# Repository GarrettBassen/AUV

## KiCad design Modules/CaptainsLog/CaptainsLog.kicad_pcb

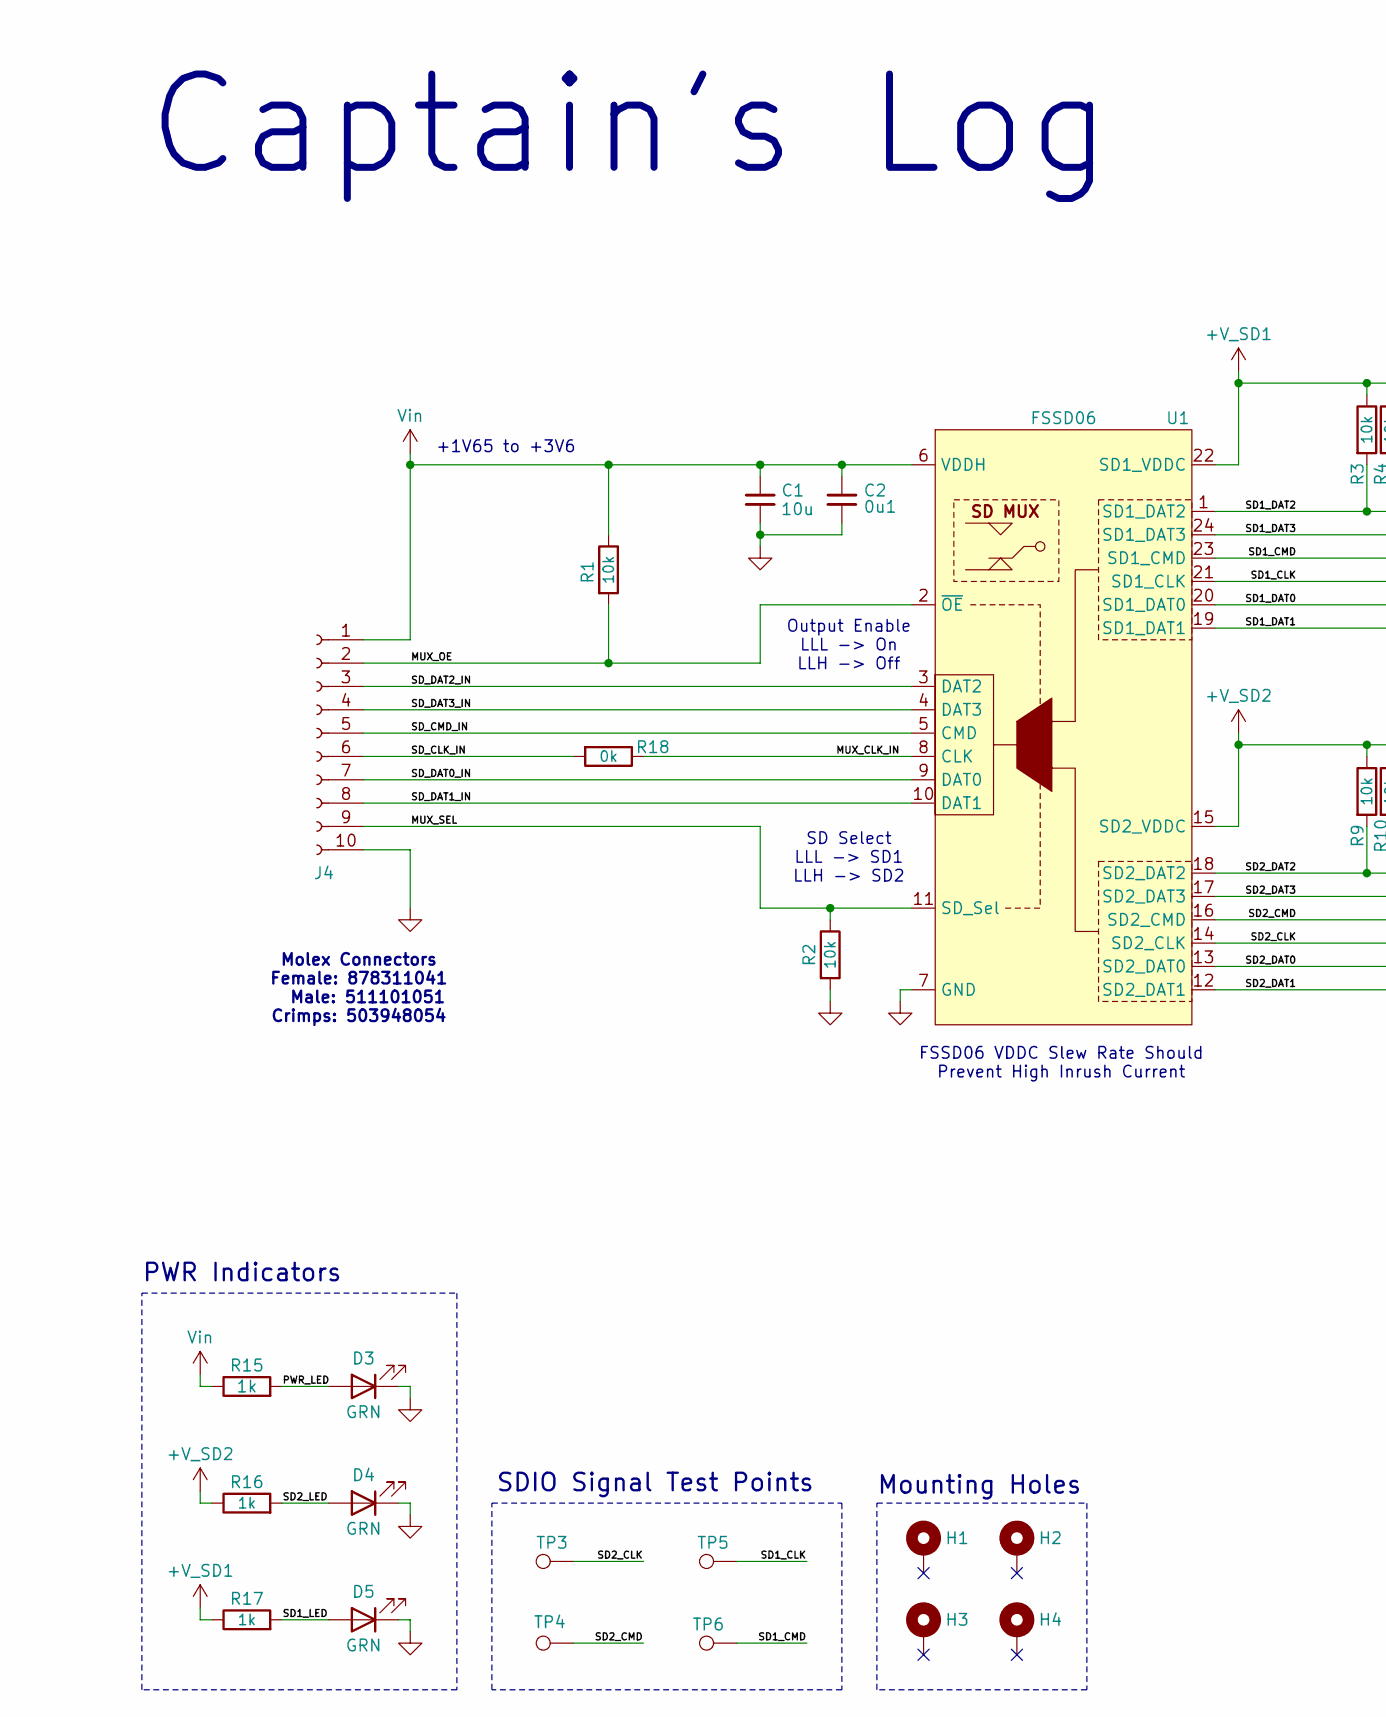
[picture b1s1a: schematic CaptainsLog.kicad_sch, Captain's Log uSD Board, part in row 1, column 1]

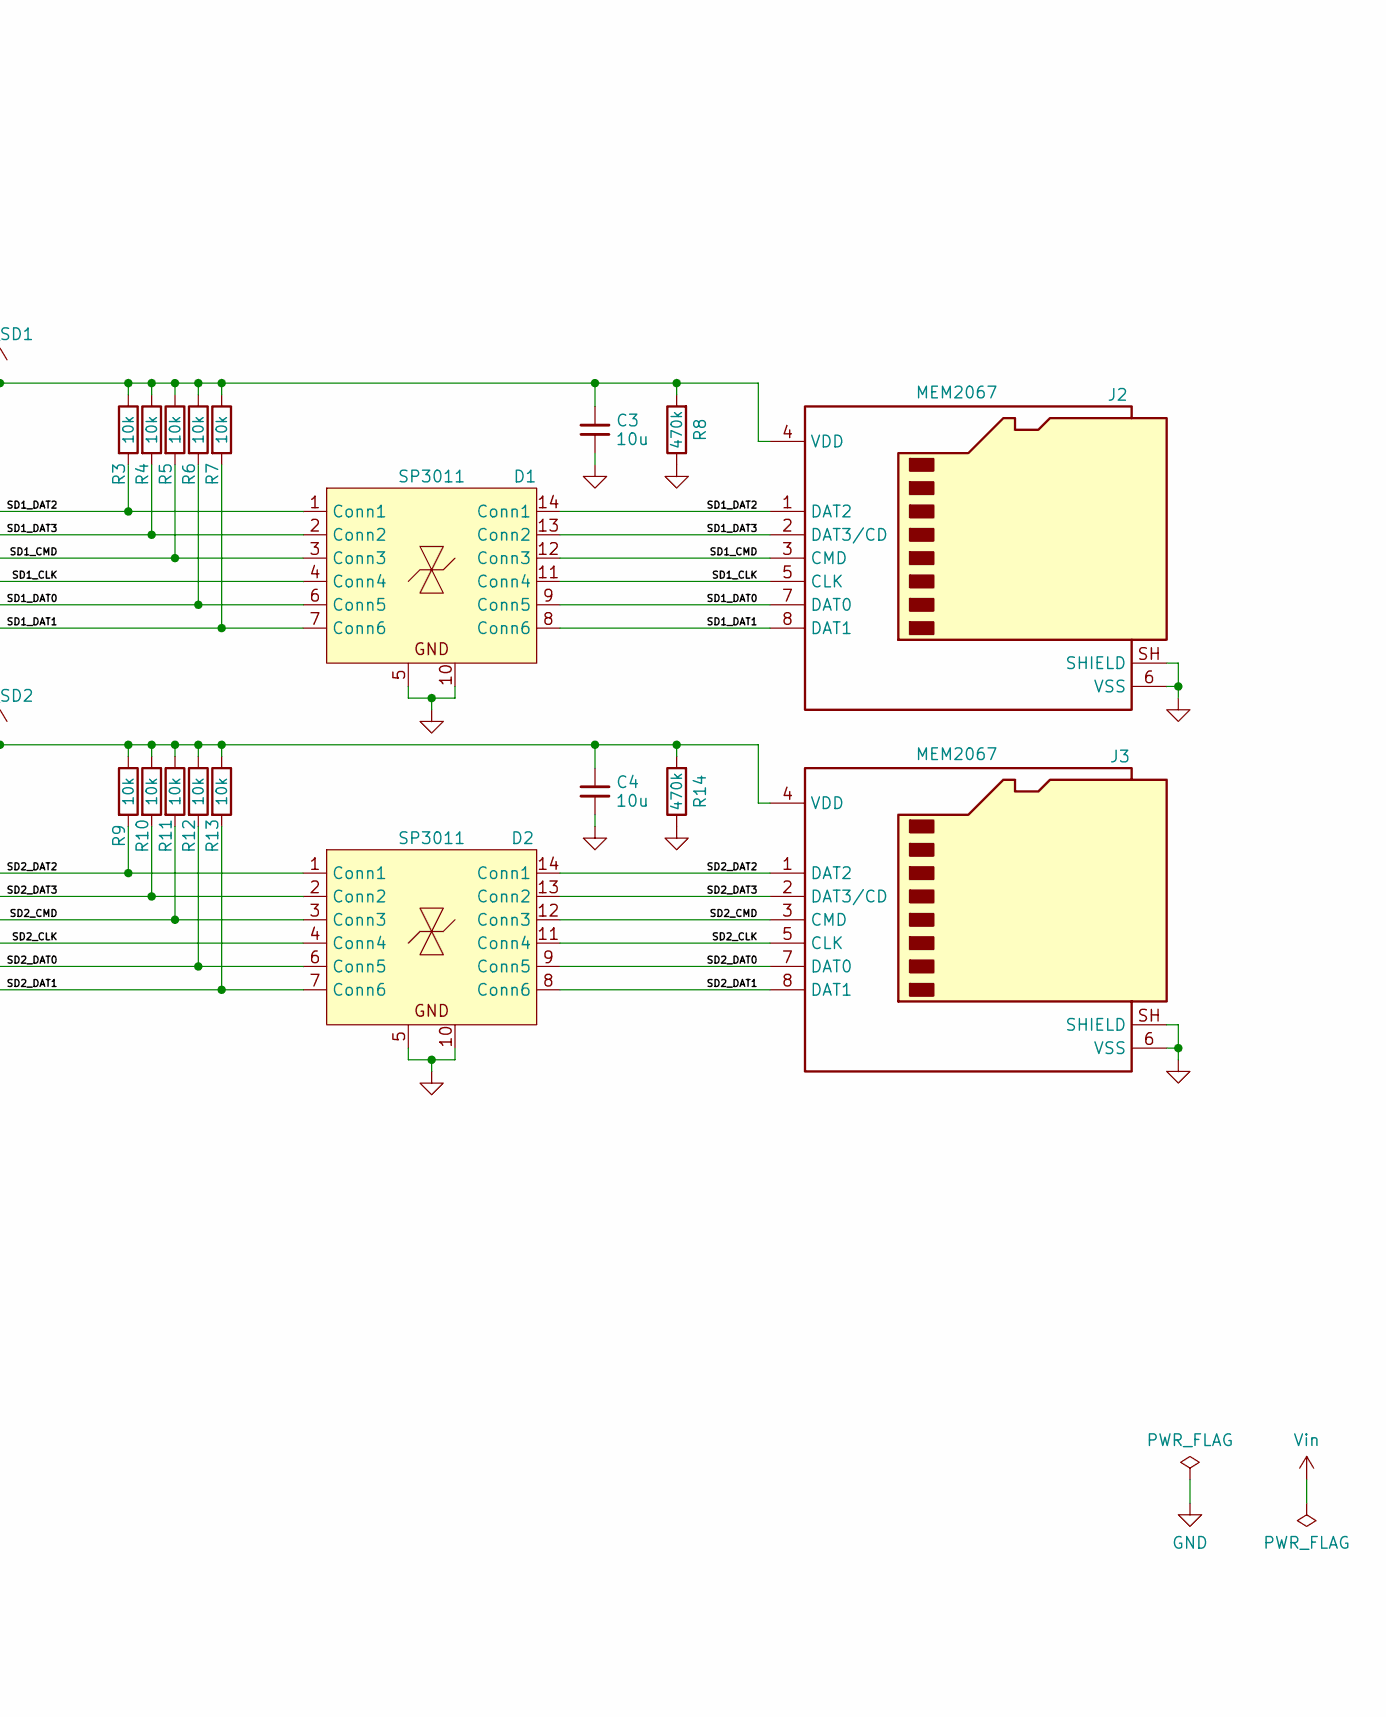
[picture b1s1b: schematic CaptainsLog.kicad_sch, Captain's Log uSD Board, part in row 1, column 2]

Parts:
C1, C3, C4: 10u; C_0603_1608Metric
C2: 0u1; C_0402_1005Metric
D1, D2: SP3011; SP3011-06UTG
D3, D4, D5: GRN; LED_0603_1608Metric
H1, H2, H3, H4: MountingHole_Pad; MountingHole_2.5mm_Pad
J2, J3: MEM2067
J4: Conn_01x10_Socket; 87831-10xx
R1, R2, R3, R4, R5, R6, R7, R9, R10, R11, R12, R13: 10k; R_0201_0603Metric
R8, R14: 470k; R_0402_1005Metric
R15, R16, R17: 1k; R_0402_1005Metric
R18: 0k; R_0201_0603Metric
TP3, TP4, TP5, TP6: TestPoint; TestPoint_Pad_D1.0mm
U1: FSSD06

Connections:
+V_SD1: C3.1, J2.4 (VDD), R3.1, R4.1, R5.1, R6.1, R7.1, R8.2, R17.1, U1.22 (SD1_VDDC)
+V_SD2: C4.1, J3.4 (VDD), R9.1, R10.1, R11.1, R12.1, R13.1, R14.2, R16.1, U1.15 (SD2_VDDC)
/MUX_CLK_IN: R18.1, U1.8 (CLK)
/MUX_OE: J4.2, R1.2, U1.2 (~OE)
/MUX_SEL: J4.9, R2.1, U1.11 (SD_Sel)
/PWR_LED: D3.2 (A), R15.2
/SD1_CLK: D1.4 (Conn4), D1.11 (Conn4), J2.5 (CLK), TP5.1 (1_1), U1.21 (SD1_CLK)
/SD1_CMD: D1.3 (Conn3), D1.12 (Conn3), J2.3 (CMD), R5.2, TP6.1 (1_1), U1.23 (SD1_CMD)
/SD1_DAT0: D1.6 (Conn5), D1.9 (Conn5), J2.7 (DAT0), R6.2, U1.20 (SD1_DAT0)
/SD1_DAT1: D1.7 (Conn6), D1.8 (Conn6), J2.8 (DAT1), R7.2, U1.19 (SD1_DAT1)
/SD1_DAT2: D1.1 (Conn1), D1.14 (Conn1), J2.1 (DAT2), R3.2, U1.1 (SD1_DAT2)
/SD1_DAT3: D1.2 (Conn2), D1.13 (Conn2), J2.2 (DAT3/CD), R4.2, U1.24 (SD1_DAT3)
/SD1_LED: D5.2 (A), R17.2
/SD2_CLK: D2.4 (Conn4), D2.11 (Conn4), J3.5 (CLK), TP3.1 (1_1), U1.14 (SD2_CLK)
/SD2_CMD: D2.3 (Conn3), D2.12 (Conn3), J3.3 (CMD), R11.2, TP4.1 (1_1), U1.16 (SD2_CMD)
/SD2_DAT0: D2.6 (Conn5), D2.9 (Conn5), J3.7 (DAT0), R12.2, U1.13 (SD2_DAT0)
/SD2_DAT1: D2.7 (Conn6), D2.8 (Conn6), J3.8 (DAT1), R13.2, U1.12 (SD2_DAT1)
/SD2_DAT2: D2.1 (Conn1), D2.14 (Conn1), J3.1 (DAT2), R9.2, U1.18 (SD2_DAT2)
/SD2_DAT3: D2.2 (Conn2), D2.13 (Conn2), J3.2 (DAT3/CD), R10.2, U1.17 (SD2_DAT3)
/SD2_LED: D4.2 (A), R16.2
/SD_CLK_IN: J4.6, R18.2
/SD_CMD_IN: J4.5, U1.5 (CMD)
/SD_DAT0_IN: J4.7, U1.9 (DAT0)
/SD_DAT1_IN: J4.8, U1.10 (DAT1)
/SD_DAT2_IN: J4.3, U1.3 (DAT2)
/SD_DAT3_IN: J4.4, U1.4 (DAT3)
GND: C1.2, C2.2, C3.2, C4.2, D1.5, D1.10, D2.5, D2.10, D3.1 (K), D4.1 (K), D5.1 (K), J2.6 (VSS), J2.SH (SHIELD), J3.6 (VSS), J3.SH (SHIELD), J4.10, R2.2, R8.1, R14.1, U1.7 (GND)
Vin: C1.1, C2.1, J4.1, R1.1, R15.1, U1.6 (VDDH)

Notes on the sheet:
FSSD06 VDDC Slew Rate Should Prevent High Inrush Current
+1V65 to +3V6
PWR Indicators
SD Select LLL -> SD1 LLH -> SD2
Molex Connectors Female: 878311041 Male: 511101051 Crimps: 503948054
Captain's Log
Mounting Holes
Output Enable LLL -> On LLH -> Off
SDIO Signal Test Points

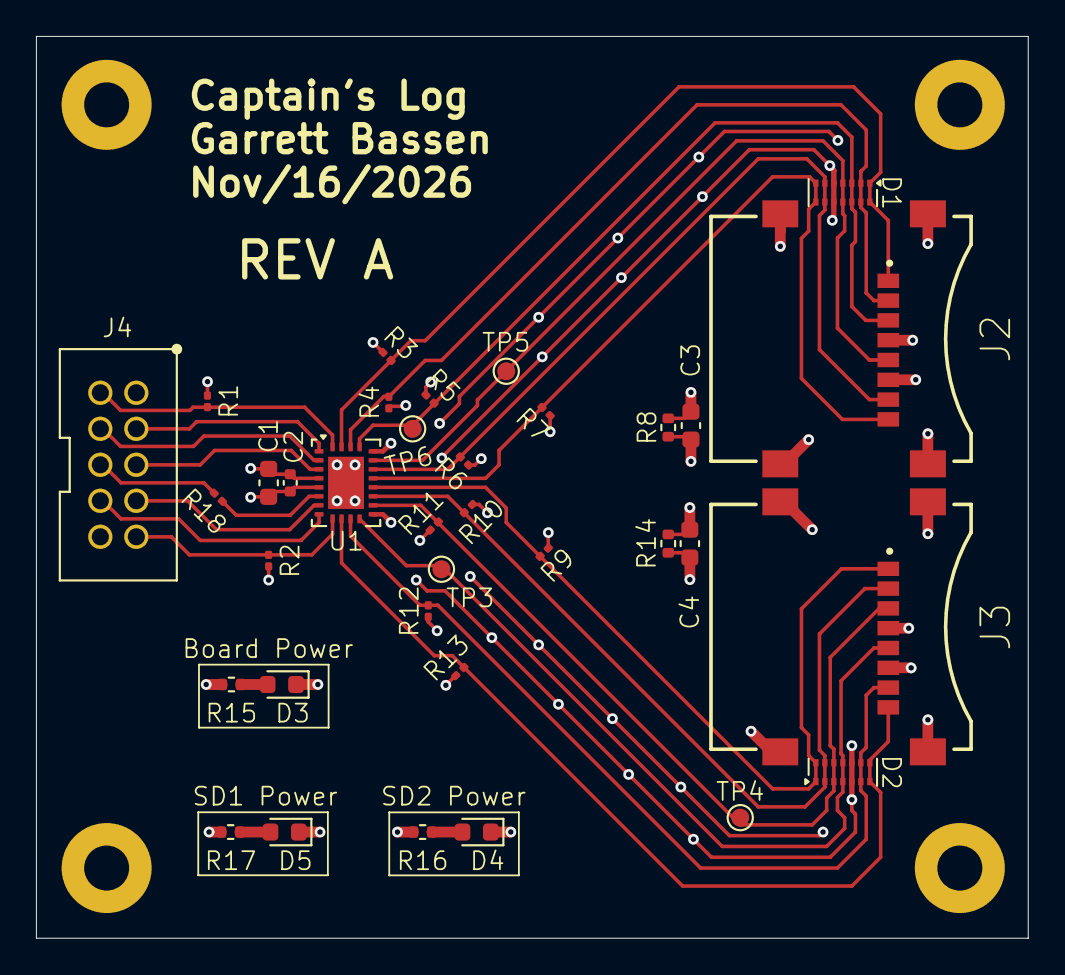
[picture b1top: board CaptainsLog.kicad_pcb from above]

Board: 4 copper layers, 55.1 x 50.1 mm, 39 parts (0 on the bottom side), 28 nets.

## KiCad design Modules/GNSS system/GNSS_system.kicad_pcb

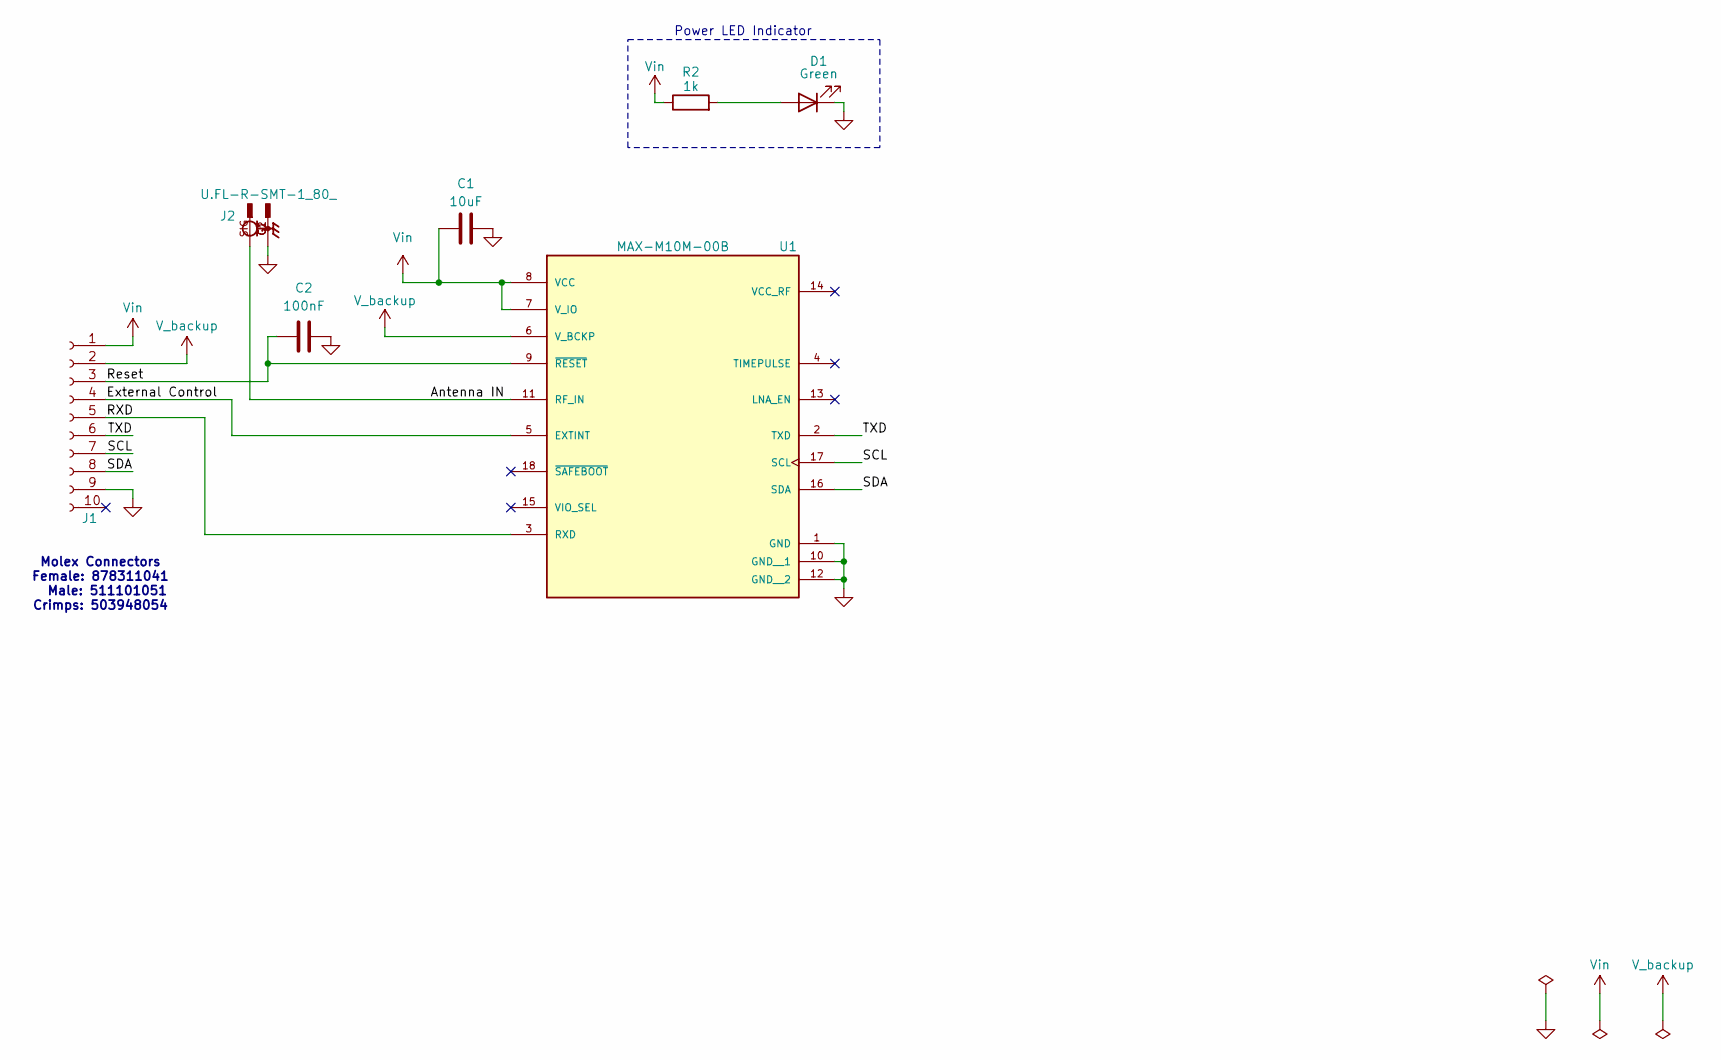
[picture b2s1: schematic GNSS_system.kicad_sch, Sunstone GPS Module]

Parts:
C1: 10uF; C_0603_1608Metric
C2: 100nF; C_0402_1005Metric
D1: Green; LED_0603_1608Metric
J1: Conn_01x10_Socket; 87831-10xx
J2: U.FL-R-SMT-1_80_; HIROSE_U.FL-R-SMT-1_80_; PARTREV Jul.1.2022
R2: 1k; R_0402_1005Metric
U1: MAX-M10M-00B; XCVR_MAX-M10M-00B; PARTREV C1

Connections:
/Antenna IN: J2.SIG, U1.11 (RF_IN)
/External Control: J1.4, U1.5 (EXTINT)
/RXD: J1.5, U1.3 (RXD)
/Reset: C2.1, J1.3, U1.9 (~RESET)
/SCL: J1.7, U1.17 (SCL)
/SDA: J1.8, U1.16 (SDA)
/TXD: J1.6, U1.2 (TXD)
GND: C1.1, C2.2, D1.1 (K), J1.9, J2.G1, J2.G2, U1.1 (GND), U1.10 (GND__1), U1.12 (GND__2)
unnamed: D1.2 (A), R2.2
V_backup: J1.2, U1.6 (V_BCKP)
Vin: C1.2, J1.1, R2.1, U1.7 (V_IO), U1.8 (VCC)

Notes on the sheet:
Power LED Indicator
Molex Connectors Female: 878311041 Male: 511101051 Crimps: 503948054

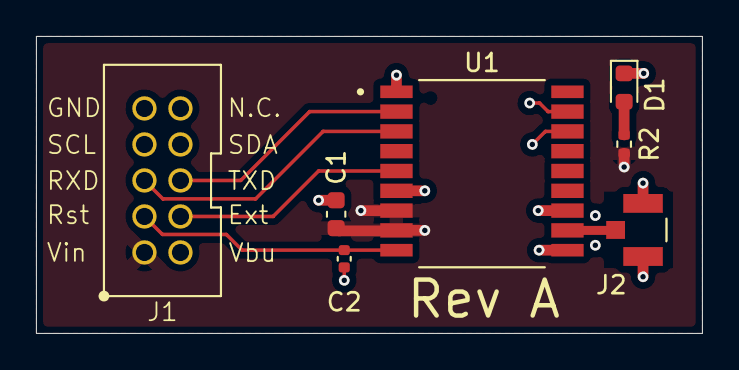
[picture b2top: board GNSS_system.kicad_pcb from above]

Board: 4 copper layers, 37.0 x 16.5 mm, 7 parts (0 on the bottom side), 11 nets.

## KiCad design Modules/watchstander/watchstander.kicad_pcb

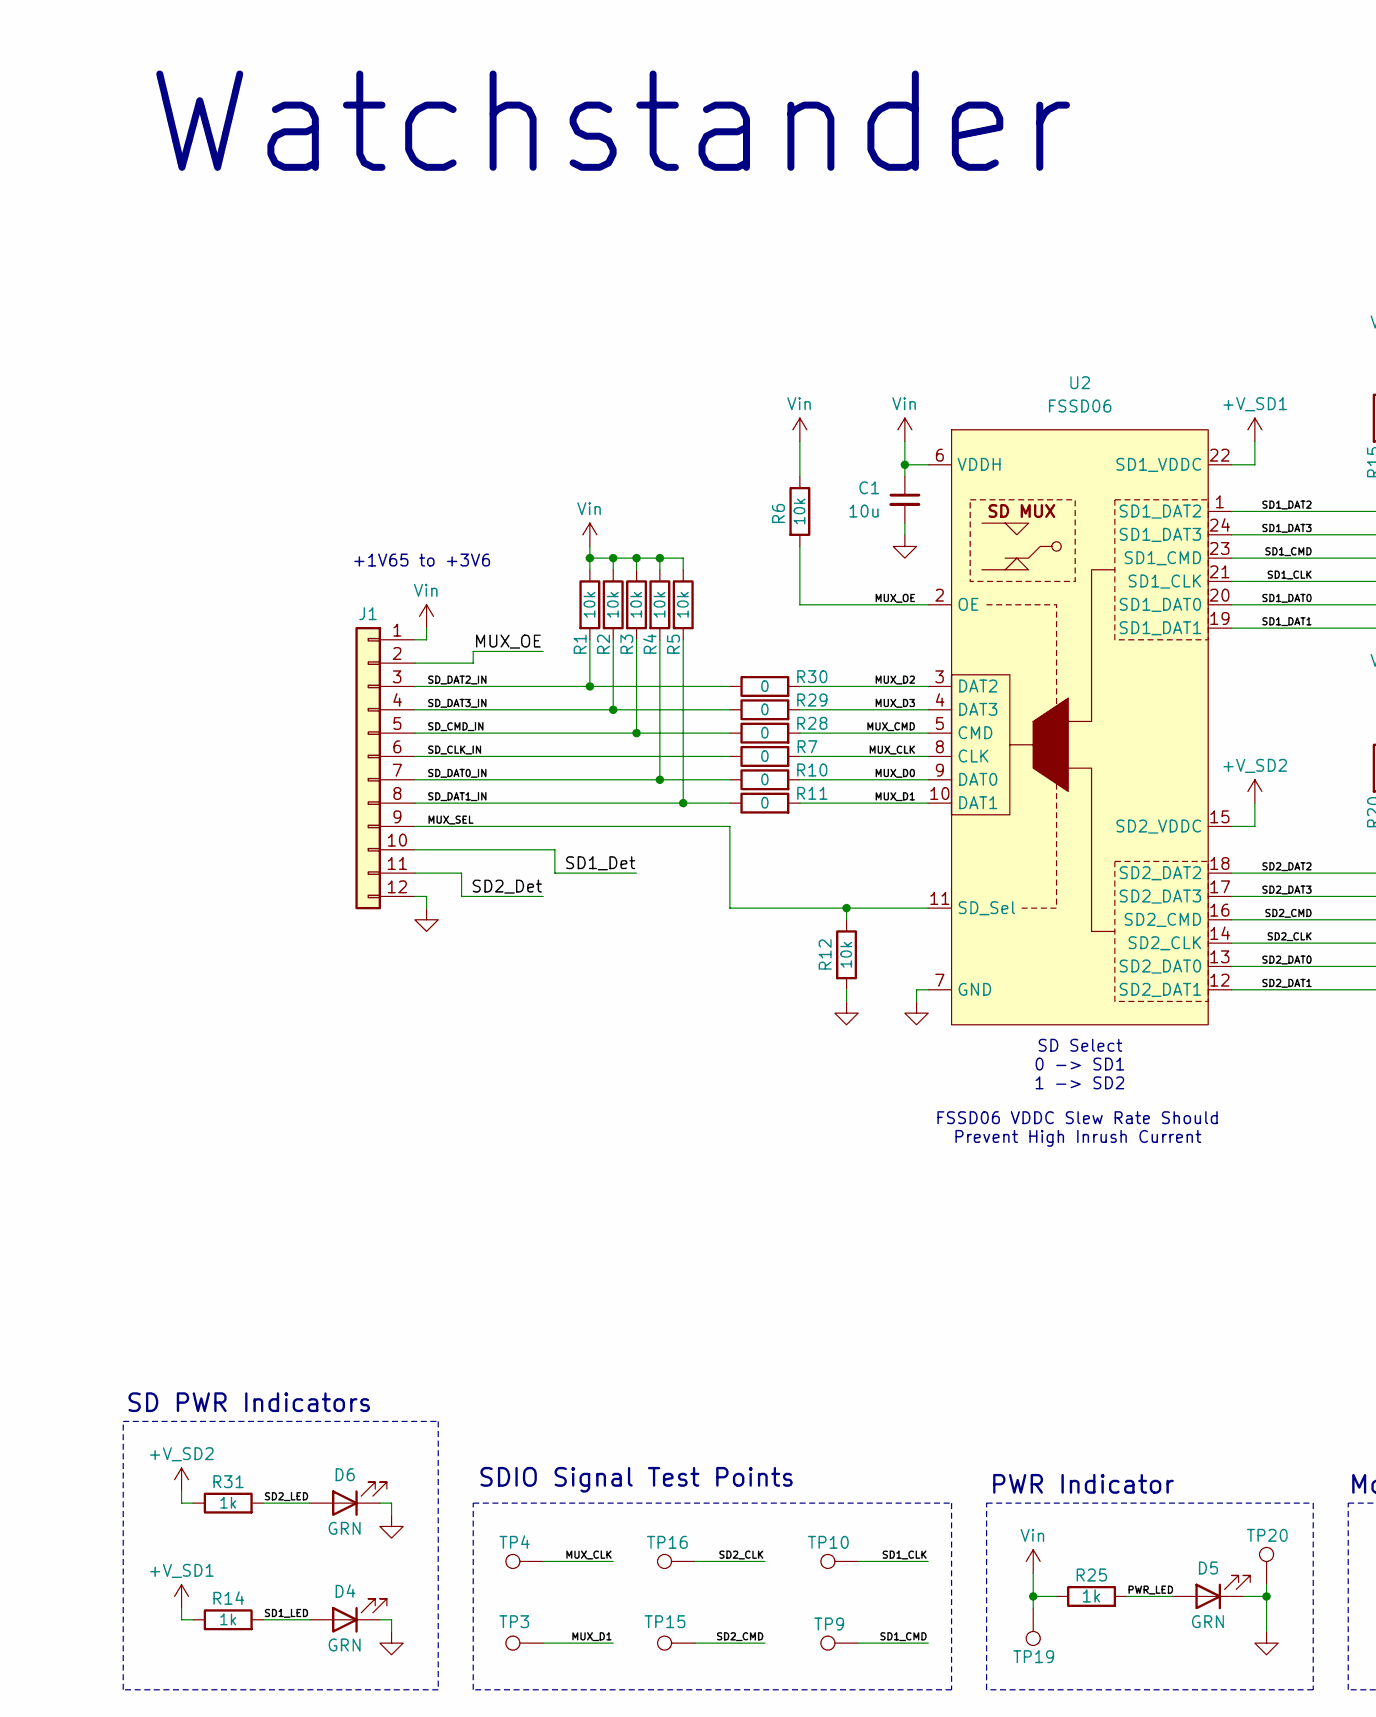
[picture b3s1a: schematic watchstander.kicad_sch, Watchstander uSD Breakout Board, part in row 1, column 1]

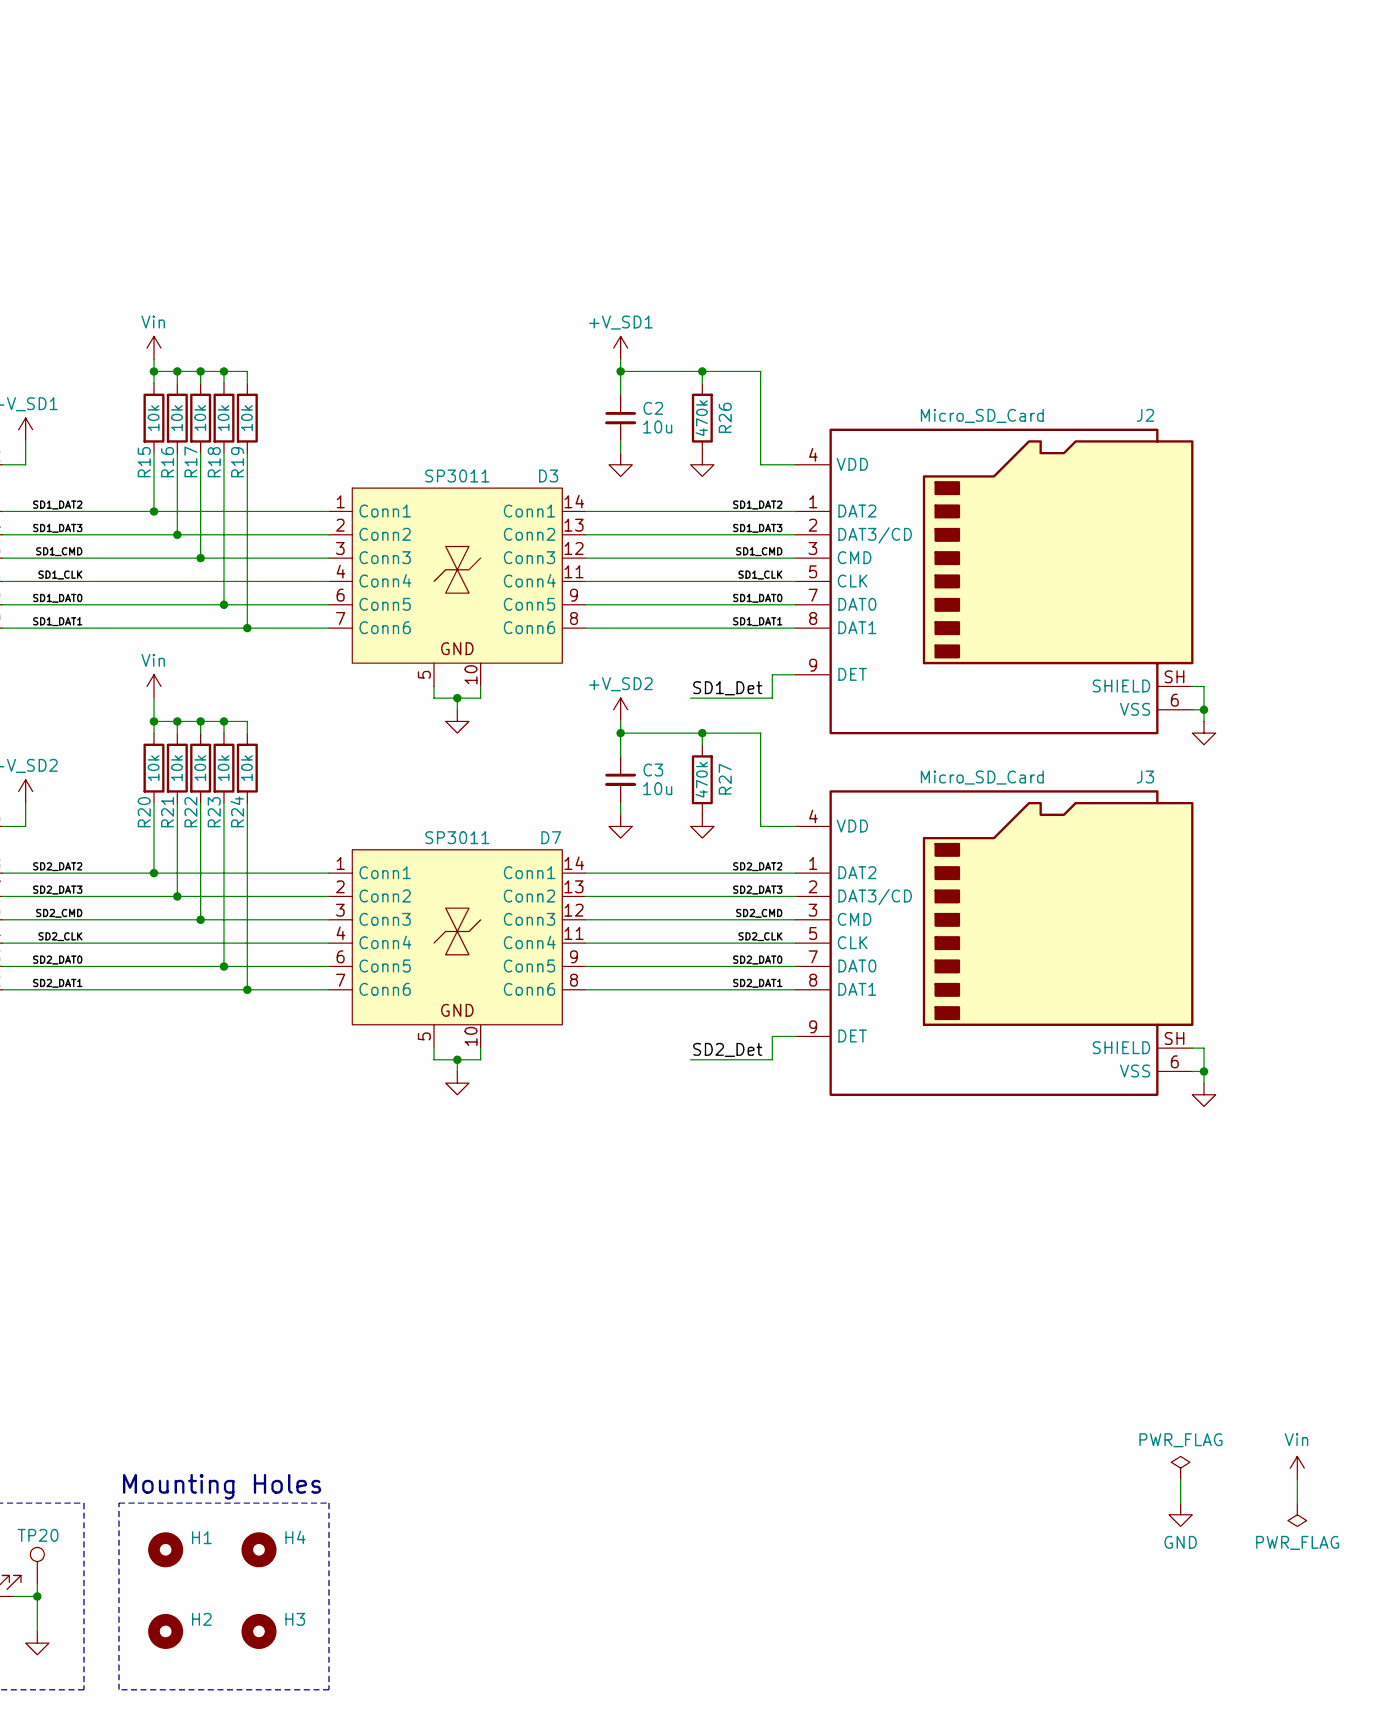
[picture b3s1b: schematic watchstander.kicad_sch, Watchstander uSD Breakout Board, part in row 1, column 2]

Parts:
C1, C2, C3: 10u; C_0603_1608Metric
D3, D7: SP3011; SP3011-06UTG
D4, D5, D6: GRN; LED_0603_1608Metric
H1, H2, H3, H4: MountingHole; MountingHole_2.5mm_Pad
J1: Conn_01x12; PinHeader_1x12_P2.54mm_Vertical
J2, J3: Micro_SD_Card; GCT_MEM2052
R1, R2, R3, R4, R5, R15, R16, R17, R18, R19, R20, R21, R22, R23, R24: 10k; R_0201_0603Metric
R6, R12: 10k; R_0603_1608Metric
R7, R10, R11, R28, R29, R30: 0; R_0201_0603Metric
R14, R25, R31: 1k; R_0402_1005Metric
R26, R27: 470k; R_0402_1005Metric
TP3, TP4, TP9, TP10, TP15, TP16: TestPoint; TestPoint_Pad_D1.0mm
TP19, TP20: TestPoint; TestPoint_THTPad_2.0x2.0mm_Drill1.0mm
U2: FSSD06

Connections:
+V_SD1: C2.1, J2.4 (VDD), R14.1, R26.2, U2.22 (SD1_VDDC)
+V_SD2: C3.1, J3.4 (VDD), R27.2, R31.1, U2.15 (SD2_VDDC)
/MUX_CLK: R7.2, TP4.1 (1_1), U2.8 (CLK)
/MUX_CMD: R28.2, U2.5 (CMD)
/MUX_D0: R10.2, U2.9 (DAT0)
/MUX_D1: R11.2, TP3.1 (1_1), U2.10 (DAT1)
/MUX_D2: R30.2, U2.3 (DAT2)
/MUX_D3: R29.2, U2.4 (DAT3)
/MUX_OE: J1.2, R6.2, U2.2 (OE)
/MUX_SEL: J1.9, R12.1, U2.11 (SD_Sel)
/PWR_LED: D5.2 (A), R25.2
/SD1_CLK: D3.4 (Conn4), D3.11 (Conn4), J2.5 (CLK), TP10.1 (1_1), U2.21 (SD1_CLK)
/SD1_CMD: D3.3 (Conn3), D3.12 (Conn3), J2.3 (CMD), R17.2, TP9.1 (1_1), U2.23 (SD1_CMD)
/SD1_DAT0: D3.6 (Conn5), D3.9 (Conn5), J2.7 (DAT0), R18.2, U2.20 (SD1_DAT0)
/SD1_DAT1: D3.7 (Conn6), D3.8 (Conn6), J2.8 (DAT1), R19.2, U2.19 (SD1_DAT1)
/SD1_DAT2: D3.1 (Conn1), D3.14 (Conn1), J2.1 (DAT2), R15.2, U2.1 (SD1_DAT2)
/SD1_DAT3: D3.2 (Conn2), D3.13 (Conn2), J2.2 (DAT3/CD), R16.2, U2.24 (SD1_DAT3)
/SD1_Det: J1.10, J2.9 (DET)
/SD1_LED: D4.2 (A), R14.2
/SD2_CLK: D7.4 (Conn4), D7.11 (Conn4), J3.5 (CLK), TP16.1 (1_1), U2.14 (SD2_CLK)
/SD2_CMD: D7.3 (Conn3), D7.12 (Conn3), J3.3 (CMD), R22.2, TP15.1 (1_1), U2.16 (SD2_CMD)
/SD2_DAT0: D7.6 (Conn5), D7.9 (Conn5), J3.7 (DAT0), R23.2, U2.13 (SD2_DAT0)
/SD2_DAT1: D7.7 (Conn6), D7.8 (Conn6), J3.8 (DAT1), R24.2, U2.12 (SD2_DAT1)
/SD2_DAT2: D7.1 (Conn1), D7.14 (Conn1), J3.1 (DAT2), R20.2, U2.18 (SD2_DAT2)
/SD2_DAT3: D7.2 (Conn2), D7.13 (Conn2), J3.2 (DAT3/CD), R21.2, U2.17 (SD2_DAT3)
/SD2_Det: J1.11, J3.9 (DET)
/SD2_LED: D6.2 (A), R31.2
/SD_CLK_IN: J1.6, R7.1
/SD_CMD_IN: J1.5, R3.2, R28.1
/SD_DAT0_IN: J1.7, R4.2, R10.1
/SD_DAT1_IN: J1.8, R5.2, R11.1
/SD_DAT2_IN: J1.3, R1.2, R30.1
/SD_DAT3_IN: J1.4, R2.2, R29.1
GND: C1.2, C2.2, C3.2, D3.5, D3.10, D4.1 (K), D5.1 (K), D6.1 (K), D7.5, D7.10, J1.12, J2.6 (VSS), J2.SH (SHIELD), J3.6 (VSS), J3.SH (SHIELD), R12.2, R26.1, R27.1, TP20.1 (1_1), U2.7 (GND)
Vin: C1.1, J1.1, R1.1, R2.1, R3.1, R4.1, R5.1, R6.1, R15.1, R16.1, R17.1, R18.1, R19.1, R20.1, R21.1, R22.1, R23.1, R24.1, R25.1, TP19.1 (1_1), U2.6 (VDDH)

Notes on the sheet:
FSSD06 VDDC Slew Rate Should Prevent High Inrush Current
SD PWR Indicators
+1V65 to +3V6
PWR Indicator
SD Select 0 -> SD1 1 -> SD2
Watchstander
Mounting Holes
SDIO Signal Test Points

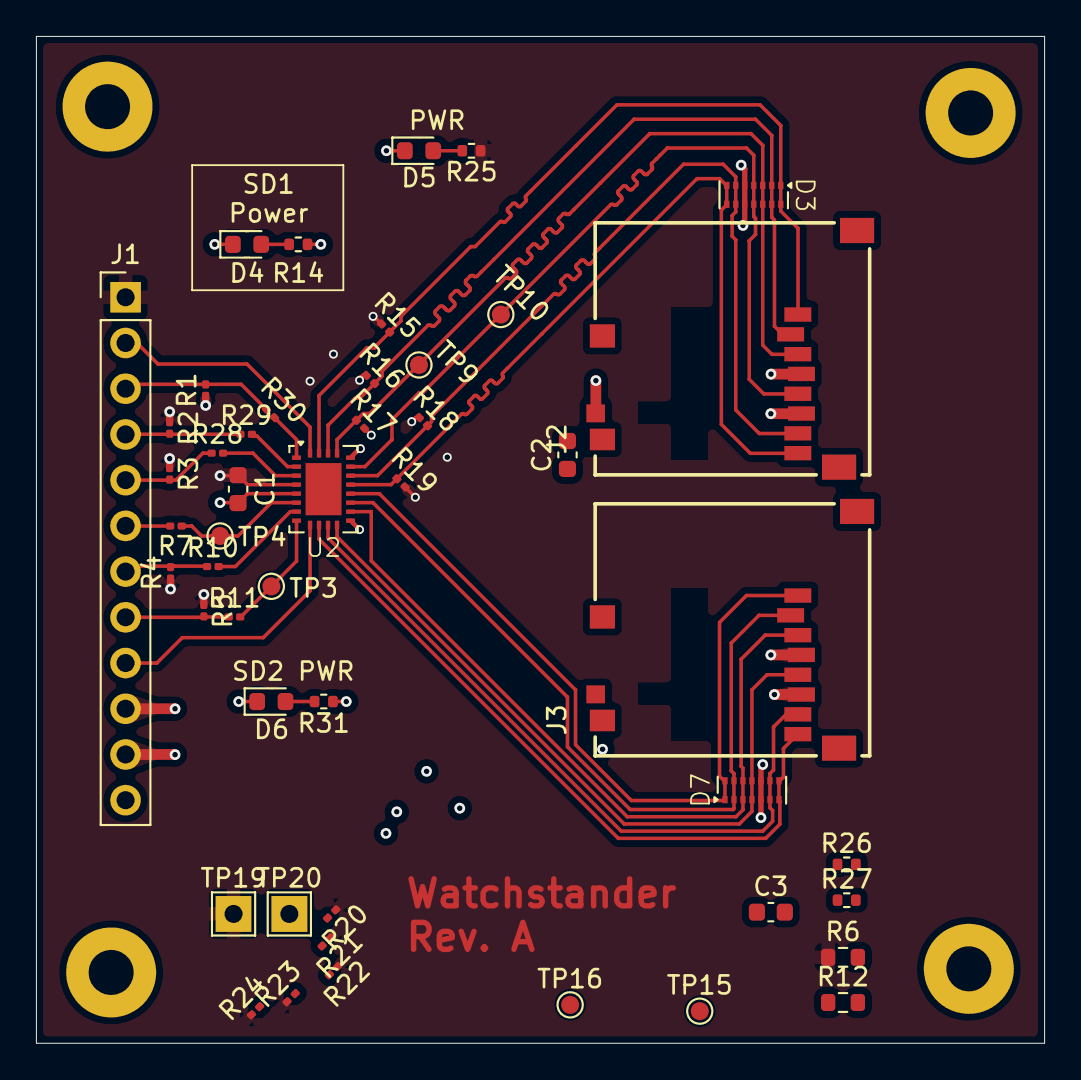
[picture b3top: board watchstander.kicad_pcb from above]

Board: 4 copper layers, 56.0 x 55.9 mm, 52 parts (0 on the bottom side), 35 nets.
